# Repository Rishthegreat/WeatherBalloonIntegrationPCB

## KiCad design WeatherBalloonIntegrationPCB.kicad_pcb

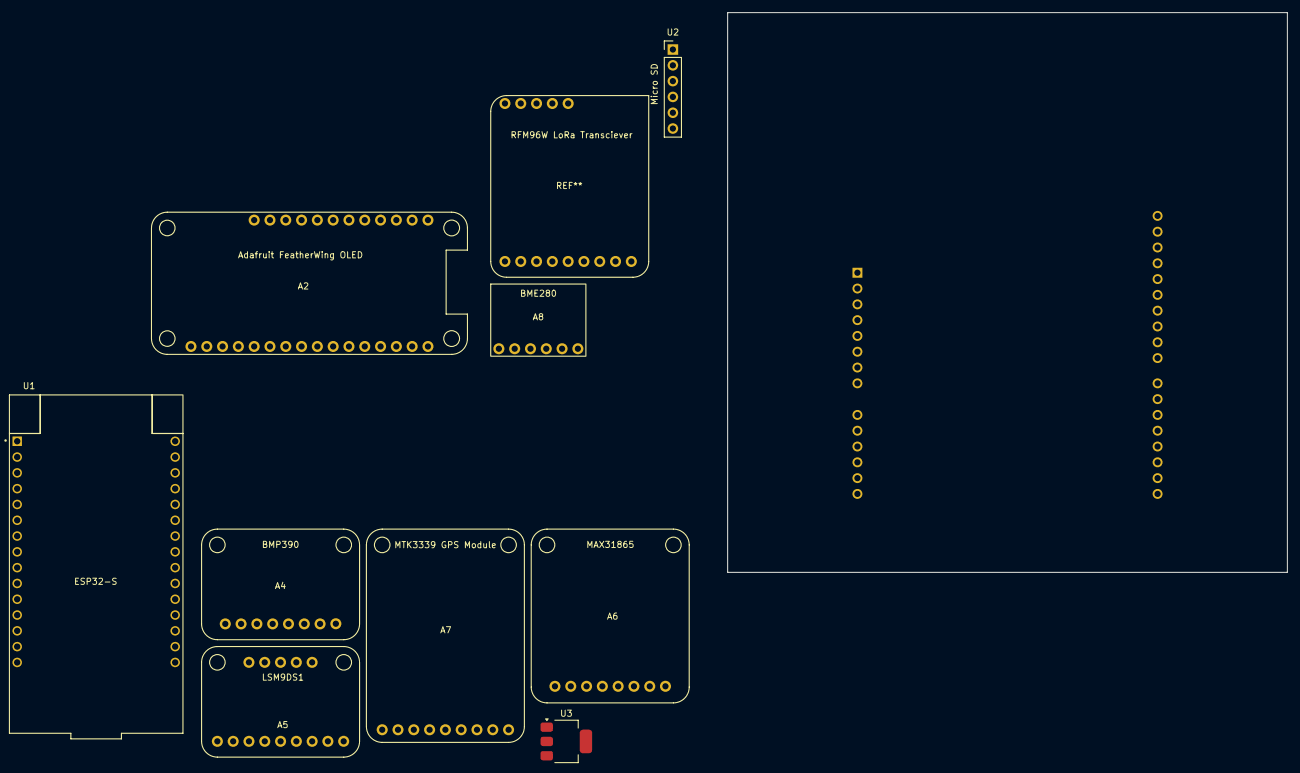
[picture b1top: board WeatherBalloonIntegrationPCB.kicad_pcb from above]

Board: 2 copper layers, 90.0 x 90.0 mm, 11 parts (1 on the bottom side), 9 nets, no tracks yet.

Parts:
A1: Arduino_UNO_R3
A2: Adafruit_FeatherWing_OLED_128x64; Adafruit FeatherWing OLED
A3: Adafruit_RFM96W_LoRa_Transciever; RFM96W LoRa Transciever
A4: Adafruit_BMP390; BMP390
A5: Adafruit_LSM9DS1; LSM9DS1
A6: Adafruit_PT100_RTD; MAX31865 PT100 RTD
A7: Adafruit_MTK3339_GPS; MTK3339 GPS Module
A8: BME280
U1: ESP-32S
U2: HiLetGo Micro SD
U3: AMS1117-3.3; SOT-223-3_TabPin2

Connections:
+3.3V: A3.1 (VIN), A4.1 (VIN), A5.1 (VIN), A6.1 (VIN), A8.1 (VCC), U2.2 (VCC), U3.2 (VO)
+BATT: A1.8 (VIN), U3.3 (VI)
CS_MAX: A1.24 (D9), A3.8 (CS), A6.7 (CS), U2.6 (CS)
GND: A1.6 (GND), A1.7 (GND), A1.29 (GND), A3.2 (GND), A4.3 (GND), A5.3 (GND), A6.2 (GND), A7.7 (GND), A8.2 (GND), U1.14 (GND), U1.24 (D18), U1.30 (D23), U2.1 (GND), U3.1 (GND)
SCK: A1.27 (D12), A3.5 (SCK), A6.4 (CLK), U2.5 (SCK)
SCL: A1.32 (SCL/A5), A4.4 (SCL), A5.4 (SCL), A8.3 (SCL)
SDA: A1.31 (SDA/A4), A4.6 (SDA), A5.5 (SDA), A8.4 (SDA)
SDI: A1.25 (D10), A3.7 (MOSI), A6.6 (SDI), U2.4 (MOSI)
SDO: A1.26 (D11), A3.6 (MISO), A6.5 (SDO), U2.3 (MISO)

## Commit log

2025-04-03 Schematics of most parts
2025-04-04 Added Symbols and Footprints
    Added symbols for:
    BMP280
    HTS221
    MAX31865
    Added footprints for:
    BMP280
2025-04-11 Adding new symbols and footprints
2025-04-14 Adding some stuff
2025-04-17 Connected most sensors
2025-04-17 some more connections
2025-04-18 Connections
